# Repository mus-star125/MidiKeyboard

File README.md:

# MidiKeyboard

## Whats a midi keyboard and why are you making it?
A MIDI keyboard is a device that lets you create and control music using keys. Instead of producing sound by itself, it sends MIDI signals to a computer or another device that can turn those signals into music.

I'm making my own custom MIDI keyboard as a hardware project for half-life week 3. I felt that this was a unique build,  a project to test my limits like, learn how keyboards work, and get more experience designing my own PCB.

## How does the keyboard work?
The keyboard work by pressing one of the keys and sending the info of the key through the MPI
Key press: When a key is pressed, the keyboard detects the input.

Microcontroller: The microcontroller processes the key press.
MIDI signal: The keyboard sends a MIDI message containing information about the note.
Computer: A computer or music software receives the MIDI message.
Sound: The software turns the MIDI information into an actual sound.

*MIDI doesn't contain the actual audio. It communicates information about notes and other musical controls.*

## devlogs

**DAY 1:**
 just started the project, its already way easier because we did PCB's in week 1 but also the guide is crystal clear! I acutally enjoyed and technically just started the schematic sketch.  Also it's the first time iim kinda changing the instructions I'm using XIAO instead of Waveshare so i'd consider that a win! Anyways, its going pretty well so far! *hah I spoke to soon*

 **DAY 2:**
 today i finished the schematic up, and used my brain to wire it all. its was pretty hard but i got it and im debating whether i should add more keys or just leave it at 7. My project is quite different from the guide but i hope it works just as well! *im still in the air btw*

 **DAY 3: The reality check**
 I finished the first pcb but then i realized its not going to work (AT ALL) and had to redo the whole schematic again :( but i finished remaking the schematic and am going to start my PCB tommorow (YAY!) we will see how that goes. here are some pic updates!

 **DAY 4:**
 I completely restarted everything  from the beginning because I messed up and nothing was working, and its still not working and i think im a bit burnt out so i will take a break and finish it up someone 
I kept missing things from my schematic, like the Xiao wasnt importing, anyways i redid it for the third time (the schematic) and changed my U1 to waveshare becasue I was soo confused at this point

 **DAY 5:**
 i finally got it, my mistake was very silly. I kept forgetting to save. Once I realised this i was so annoyed at my mistake lol. Anyways thats how we learn :) I made my footprints circles but am not sure if they are going to work or not

I finished the schematic but was struggling with the footprints at this point and just couldn't figure out how to make it like piano key whihc I ended up turning into circles in the (kinda shape) of a flower 

**DAY 6: LOCKK IN AND FINISH!**
As you can guess, today is day 6, I
 spent 2 hours perfecting i did the wiring and deleted on of the flowers cuz it WAS NOT wirin. I also uploaded all the files on github and did my readme, yoo i still gotta do the BOM 

## Lessons
This project taught me that things don't always work the way you expect them to, especially when you're designing something yourself.

I had to redo my schematic multiple times because I kept missing things, and I learned the hard way that forgetting to save can cause a LOT of unnecessary frustration.

I also learned that it's okay to change your original design. I started with the idea of making piano keys, but when I couldn't figure out how to create the footprints properly, I decided to experiment with a different layout.

The biggest lesson for me was to save my work regularly, double-check my schematic before moving on to the PCB, and take breaks when I'm getting frustrated instead of repeatedly restarting everything.

Even though I had to redo a lot of things, I learned more from the mistakes than I probably would have if everything had worked perfectly the first time.

I'm still figuring things out, but that's part of the process!

## Bill Of Materials (BOM)

| Component | Quantity | Purpose | Price |
|---|---:|---|---:|
| Waveshare microcontroller board | 1 | Processes key inputs and handles MIDI communication | $16.78 |
| Key switches / buttons | 7 | Detect which keys are pressed | $1.71|
| Custom PCB | 1 | Holds and electrically connects the components | $5.20 |
| Rotary Encoder EC11  |1 | control volume |$1.47|
| rgb led | 3 | add lighting to the keyboard | $1.42 |
| shipping |--- |--- | 8 |

**Total estimated cost:35** 

**(MORE PHOTOS IN THE IMAGES!)**

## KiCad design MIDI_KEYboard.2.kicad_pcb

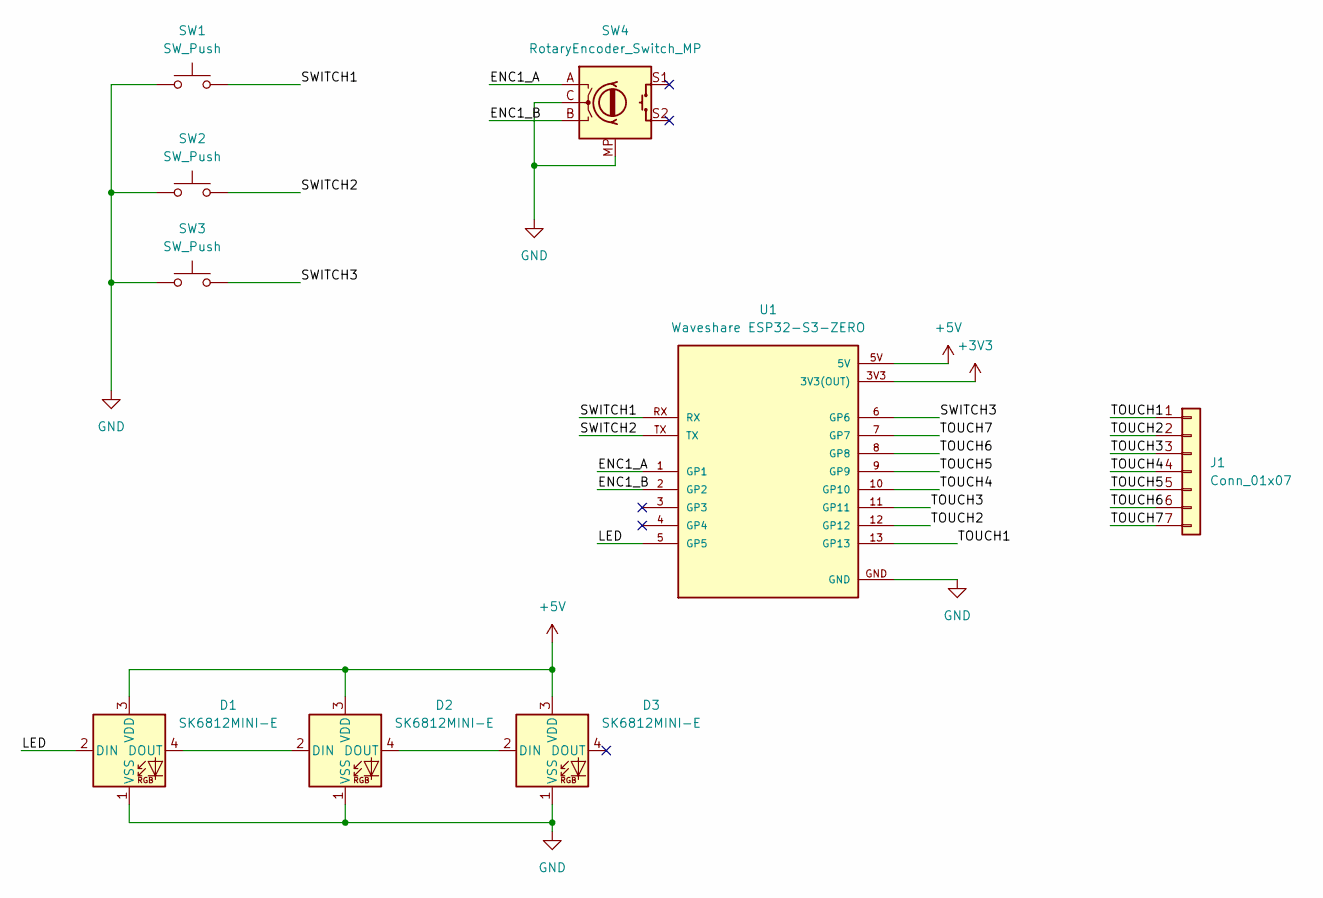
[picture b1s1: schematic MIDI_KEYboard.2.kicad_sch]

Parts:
D1, D2, D3: SK6812MINI-E; LED_SK6812MINI-E_3.2x2.8mm_P1.5mm_ReverseMount
J1: Conn_01x07; midikeys
SW1, SW2, SW3: SW_Push; Kailh Choc Low-Profile Switches
SW4: RotaryEncoder_Switch_MP; RotaryEncoder_Alps_EC11E_Vertical_H20mm
U1: Waveshare ESP32-S3-ZERO; Waveshare ESP32-S3-Zero; PARTREV NA

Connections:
+3V3: U1.3V3 (3V3(OUT))
+5V: D1.3 (VDD), D2.3 (VDD), D3.3 (VDD), U1.5V
/<NO NET>: J1.5, U1.9 (GP9)
/ENC1_A: SW4.A, U1.1 (GP1)
/ENC1_B: SW4.B, U1.2 (GP2)
/LED: D1.2 (DIN), U1.5 (GP5)
/SWITCH1: SW1.2, U1.RX
/SWITCH2: SW2.2, U1.TX
/SWITCH3: SW3.2, U1.6 (GP6)
/TOUCH1: J1.1, U1.13 (GP13)
/TOUCH2: J1.2, U1.12 (GP12)
/TOUCH3: J1.3, U1.11 (GP11)
/TOUCH4: J1.4, U1.10 (GP10)
/TOUCH6: J1.6, U1.8 (GP8)
/TOUCH7: J1.7, U1.7 (GP7)
GND: D1.1 (VSS), D2.1 (VSS), D3.1 (VSS), SW1.1, SW2.1, SW3.1, SW4.C, SW4.MP, U1.GND
unnamed: D1.4 (DOUT), D2.2 (DIN)
unnamed: D2.4 (DOUT), D3.2 (DIN)

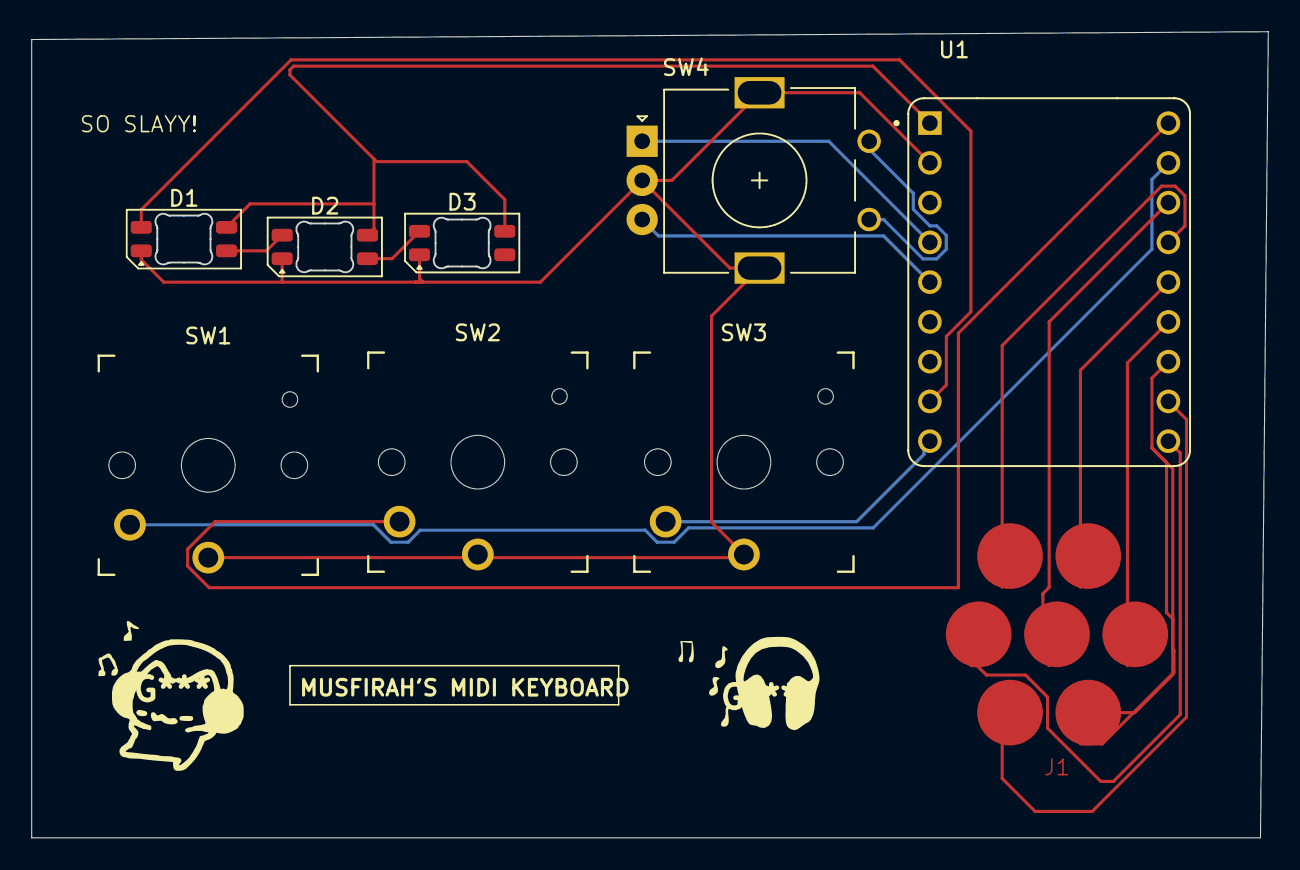
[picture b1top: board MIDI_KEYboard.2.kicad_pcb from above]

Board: 2 copper layers, 79.0 x 51.5 mm, 9 parts (0 on the bottom side), 17 nets.
